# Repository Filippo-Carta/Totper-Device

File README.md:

# ESP32 TOTP Firmware

TOTP (Time-based One-Time Password) generator running on an ESP32-C3, controlled via USB serial from the companion Android app. No WiFi, no cloud, no internet connection required at any point.

## Overview

TOTP secrets are stored exclusively on the physical ESP32 device in non-volatile storage (NVS). The device has no network interface — time is supplied by the Android app over USB serial each time it connects. Once synced, the ESP32 tracks elapsed time internally using its own clock, so codes remain valid for the entire session.

Access to the device is protected by a 5-digit PIN entered via two physical buttons. After 5 failed attempts, all stored accounts are permanently wiped and the device reboots.

## Hardware
All of the necessary schematic are available in the /schematic/ folder in the repository. You can print the pcb by exporting the files and sending them to a pcb manufacturer.
| Component | Details |
|---|---|
| Microcontroller | ESP32-C3 |
| Display | SSD1306 OLED, 128x32, I2C |
| Button 1 (Cycle) | GPIO 5 — cycles digits / switches account |
| Button 2 (Confirm) | GPIO 6 — confirms digit / advances to next |
| I2C SDA | GPIO 4 |
| I2C SCL | GPIO 3 |

## Dependencies

Install these libraries via the Arduino Library Manager or PlatformIO:

- [Adafruit SSD1306](https://github.com/adafruit/Adafruit_SSD1306)
- [Adafruit GFX Library](https://github.com/adafruit/Adafruit-GFX-Library)
- `Preferences` — built into the ESP32 Arduino core
- `mbedtls/md.h` — built into the ESP32 Arduino core

## Security Warning

This firmware stores TOTP secrets in ESP32 NVS flash **in plaintext**. NVS is not encrypted by default.

This means that anyone with physical access to the device and a USB connection can dump the entire flash contents using standard tools and read every stored secret directly — regardless of the PIN. The PIN only protects the serial interface. It does not protect the flash memory itself.

**If you do not enable flash encryption, physical possession of the device is equivalent to full access to all your TOTP secrets.**

Without flash encryption this device should be treated as a convenience tool only, not as a secure hardware token. With flash encryption enabled, physical attacks become significantly harder.

## Serial Protocol

Communication runs at **115200 baud, 8N1** over USB CDC. All commands are newline-terminated (`\n`).

| Command | Response | Auth required |
|---|---|---|
| `TIME <unix>` | `OK:time_set:<unix>` | No |
| `STATUS` | `OK:ready:<n>` | Yes |
| `LIST` | JSON array `[{index, name}, ...]` | Yes |
| `ADD <n> <base32>` | `OK:added:<idx>:<n>` | Yes |
| `REMOVE <idx>` | `OK:removed:<idx>:<n>` | Yes |
| `CLEAR` | `OK:cleared` | No |

Any command requiring auth while the device is locked returns `ERR:locked`.

`TIME` and `CLEAR` are always permitted regardless of lock state. `CLEAR` wipes all accounts and reboots the device.

### Constraints

- Account name: maximum 12 characters
- Base32 secret: minimum 8 characters, uppercase, standard Base32 alphabet

## PIN System

The PIN is 5 digits, entered using the two physical buttons:

- **Cycle button** — increments the current digit (0-9, wraps around)
- **Confirm button** — confirms the digit and advances to the next position

On first boot, the device enters a PIN setup flow before doing anything else. The PIN is stored in NVS alongside the accounts.

To change the PIN, hold the **Confirm button** while powering on the device. The change flow requires the current PIN before setting a new one.

After **5 consecutive wrong PIN attempts**, all data is wiped via `nvsClearAll()` and the device restarts.

## Time Sync

The device has no RTC and no network access. On every USB connection, the Android app sends:

```
TIME <unix_seconds>
```

The firmware records the Unix timestamp and the value of `millis()` at that moment. From then on, the current time is calculated as:

```
currentTime = baseUnix + (millis() - baseMillis) / 1000
```

Until a `TIME` command is received, the display shows "Waiting for time sync" and no TOTP codes are generated.

## TOTP Implementation

The firmware implements RFC 6238 using HMAC-SHA1 from the mbedTLS library (bundled with the ESP32 Arduino core). The time step is 30 seconds and codes are 6 digits.

```
counter = currentTime / 30
TOTP    = HOTP(secret, counter)
```

## NVS Storage Layout

All data is stored under the `totp` namespace in NVS flash.

| Key | Type | Description |
|---|---|---|
| `pin` | String | 5-digit PIN |
| `count` | Int | Number of stored accounts |
| `name_N` | String | Account name at index N |
| `sec_N` | String | Base32 secret at index N |
| `fail_cnt` | Int | Consecutive failed PIN attempts |

## Companion App

The Android app that communicates with this firmware is available at:

[https://github.com/filippo-carta/Totper](https://github.com/Filippo-Carta/Totper)

## License

Copyright Filippo Carta — [CC BY-NC-ND 4.0](https://creativecommons.org/licenses/by-nc-nd/4.0/)

Free to use and share with attribution. Modification and commercial use are not permitted.

## HAVE FUN!

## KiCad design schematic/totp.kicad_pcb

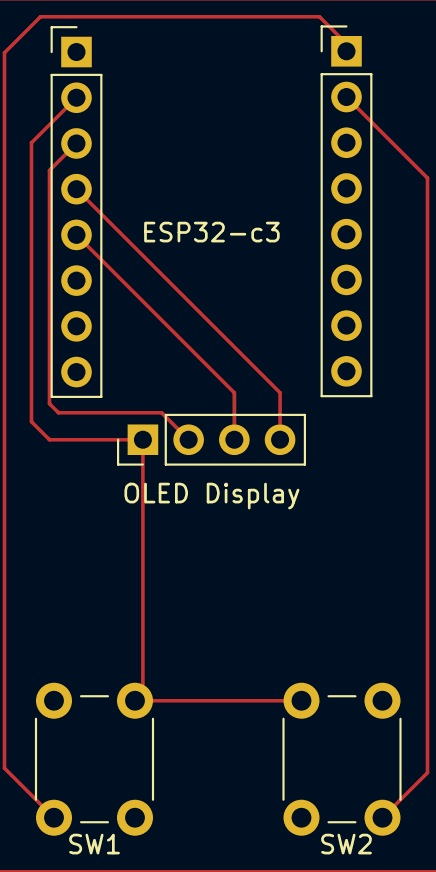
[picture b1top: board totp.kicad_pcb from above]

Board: 2 copper layers, 5 parts (0 on the bottom side), 6 nets.

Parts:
J1: Conn_01x04_Pin; PinHeader_1x04_P2.54mm_Vertical
J2, J3: Conn_01x08_Pin; PinHeader_1x08_P2.54mm_Vertical
SW1, SW2: SW_Push_Dual; SW_PUSH_6mm

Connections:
unnamed: J1.1, J3.2, SW1.2, SW2.2
unnamed: J1.2, J3.3
unnamed: J1.3, J3.5
unnamed: J1.4, J3.4
unnamed: J2.1, SW1.1
unnamed: J2.2, SW2.1

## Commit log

2026-03-28 Add initial firmware.
2026-03-28 Fix README.md
2026-03-28 Update README with security warning and hardware details
    Added security warning about plaintext TOTP secrets and flash encryption.

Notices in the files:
README.md:
License: CC BY-NC-ND 4.0
